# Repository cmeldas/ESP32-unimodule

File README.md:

# ESP32 universal PCB for home automation

# Using TTGO-T Display 
https://github.com/Xinyuan-LilyGO/TTGO-T-Display

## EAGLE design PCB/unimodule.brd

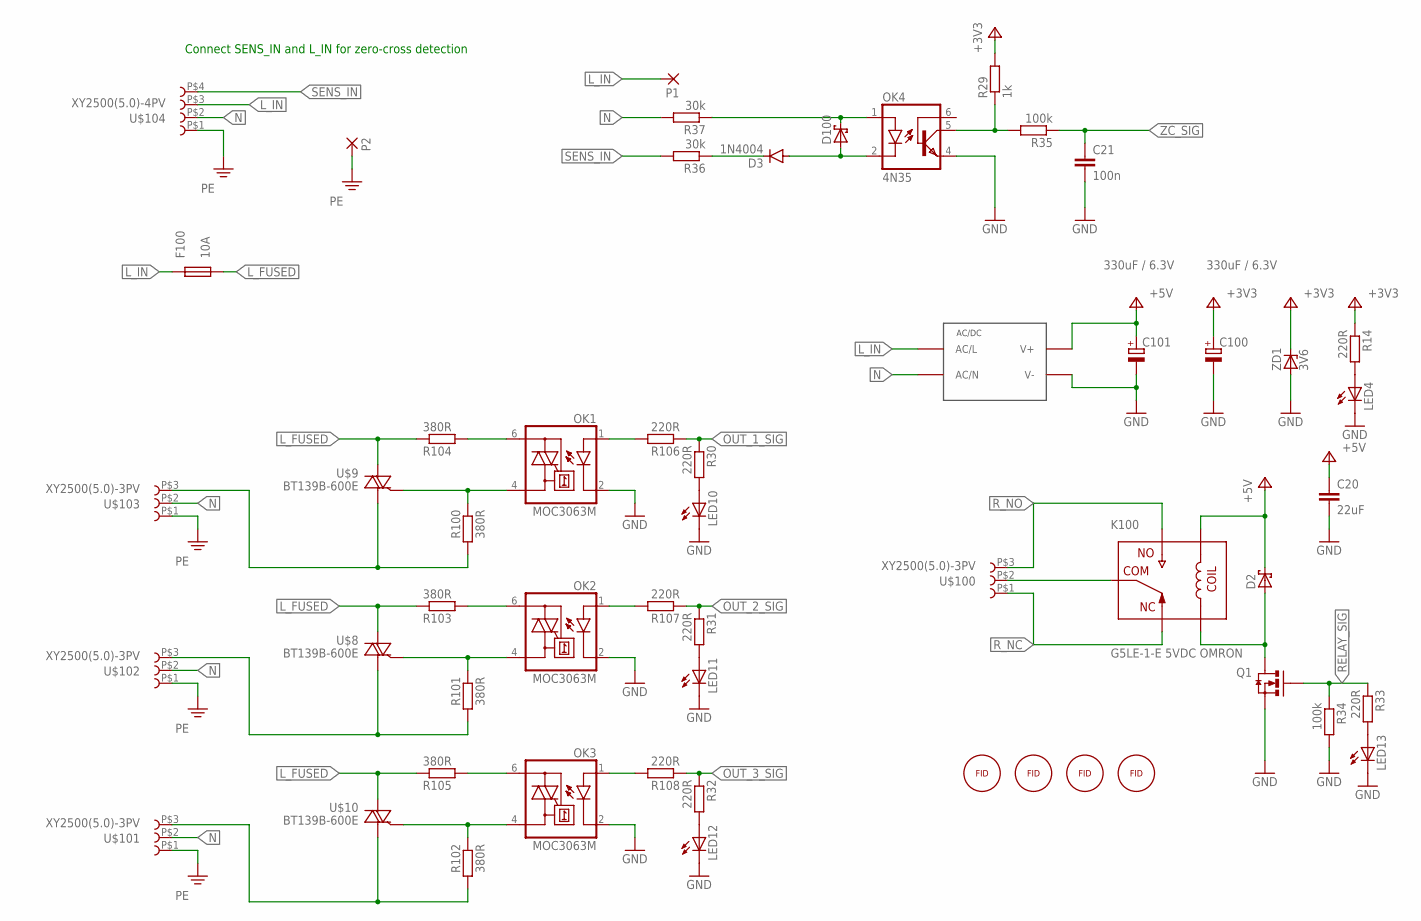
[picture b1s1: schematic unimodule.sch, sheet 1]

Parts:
C20: 22uF; C1206
C21: 100n; C0603
C100: 330uF / 6.3V; E2,5-7
C101: 330uF / 6.3V; E2,5-6
D2: PMEG4005EH; SOD123F
D3: 1N4004; DO41-10
D100: BAT46; SOD123F
F100: 10A; SCHURTER_0751.0056_5X20
FD1, FD2, FD100, FD101: FIDUCIAL-MARKER2MM; 1-2MM-FIDUCIAL
K100: G5LE-1-E 5VDC OMRON; JSM1-12V-5
LED4, LED10, LED11, LED12, LED13: LED0603; LED-0603
OK1, OK2, OK3: MOC3063M; DIL06
OK4: 4N35; DIL06
P1: WIRE-PAD1MM; THT-PAD_0.5MM
P2: WIRE-PAD3MM; 6MM2
Q1: 2N7002; PG-SOT23
R14, R30, R31, R32, R33, R106, R107, R108: 220R; R0603
R29: 1k; R0603
R34, R35: 100k; R0603
R36, R37: 30k; 0207/10
R100, R101, R102, R103, R104, R105: 380R; R1206
U$8, U$9, U$10: BT139B-600E; D2PACK
U$100, U$101, U$102, U$103: XY2500(5.0)-3PV; XY2500V-B_3P
U$104: XY2500(5.0)-4PV; XY2500V-B_4P
U$105: IRM-03-05; IRM-03
ZD1: 3V6; SOD323-W

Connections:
+3V3: C100.+, R14.1, R29.2, ZD1.C; also elsewhere on the board
+5V: C20.1, C101.+, D2.C, K100.2, U$105.V+; also elsewhere on the board
GND: C20.2, C21.2, C100.-, C101.-, LED4.C, LED10.C, LED11.C, LED12.C, LED13.C, OK1.2 (C), OK2.2 (C), OK3.2 (C), OK4.4 (EMI), Q1.2 (S), R34.2, U$105.V-, ZD1.A; also elsewhere on the board
L_FUSED: F100.I_1 (1), F100.I_2 (1), F100.I_3 (1), R103.1, R104.1, R105.1, U$8.2 (A2), U$9.2 (A2), U$10.2 (A2)
L_IN: F100.O_1 (2), F100.O_2 (2), F100.O_3 (2), P1.P$1, U$104.P$3 (3), U$105.AC/L
L_OUT_1: R100.2, U$9.1 (A1), U$103.P$3 (3)
L_OUT_2: R101.2, U$8.1 (A1), U$102.P$3 (3)
L_OUT_3: R102.2, U$10.1 (A1), U$101.P$3 (3)
N: R37.2, U$101.P$2 (2), U$102.P$2 (2), U$103.P$2 (2), U$104.P$2 (2), U$105.AC/N
unnamed: D3.A, D100.A, OK4.2 (C)
unnamed: D3.C, R36.1
unnamed: D100.C, OK4.1 (A), R37.1
unnamed: OK3.6 (A2), R105.2
unnamed: OK3.4 (A1), R102.1, U$10.3 (G)
unnamed: OK2.6 (A2), R103.2
unnamed: OK3.1 (A), R108.2
unnamed: OK2.4 (A1), R101.1, U$8.3 (G)
unnamed: OK2.1 (A), R107.2
unnamed: OK1.6 (A2), R104.2
unnamed: OK1.4 (A1), R100.1, U$9.3 (G)
unnamed: OK1.1 (A), R106.2
unnamed: LED10.A, R30.2
unnamed: LED11.A, R31.2
unnamed: LED12.A, R32.2
unnamed: D2.A, K100.5, Q1.3 (D)
unnamed: LED13.A, R33.2
unnamed: LED4.A, R14.2
OUT_1_SIG: R30.1, R106.1; also elsewhere on the board
OUT_2_SIG: R31.1, R107.1; also elsewhere on the board
OUT_3_SIG: R32.1, R108.1; also elsewhere on the board
PE: P2.P$1, P2.P$2, P2.P$5, P2.P$6, P2.P$7, P2.P$8, P2.P$9, P2.P$10, P2.P$11, U$101.P$1 (1), U$102.P$1 (1), U$103.P$1 (1), U$104.P$1 (1)
RELAY_SIG: Q1.1 (G), R33.1, R34.1; also elsewhere on the board
R_C: K100.1, U$100.P$2 (2)
R_NC: K100.4, U$100.P$1 (1)
R_NO: K100.3, U$100.P$3 (3)
SENS_IN: R36.2, U$104.P$4 (4)
ZC: OK4.5 (COL), R29.1, R35.2
ZC_SIG: C21.1, R35.1; also elsewhere on the board

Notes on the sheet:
Connect SENS_IN and L_IN for zero-cross detection

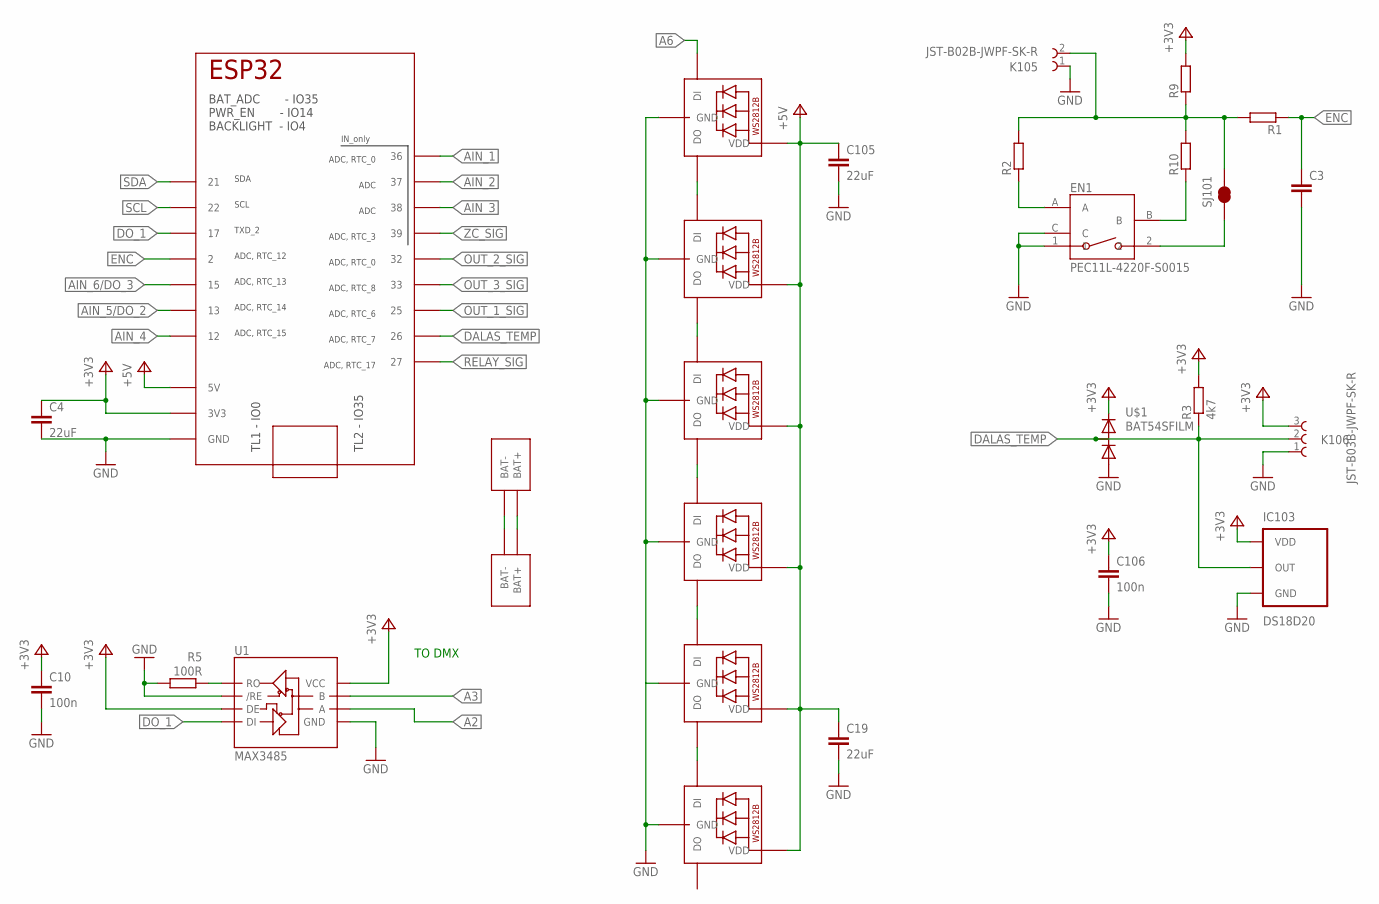
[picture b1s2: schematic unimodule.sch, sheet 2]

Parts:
C3: C-EUC0603; C0603
C4, C19, C105: 22uF; C1206
C10, C106: 100n; C0603
C11: DISP_BATSMD; BAT_SMD
C107: DISP_BAT2,54; BAT_THT_254
EN1: PEC11L-4220F-S0015
IC1: TTGO_DISP; TTGO_DISP_DEFAULT
IC103: DS18D20; TO92
K105: JST-B02B-JWPF-SK-R
K106: JST-B03B-JWPF-SK-R
LED1, LED2, LED3, LED5, LED6, LED14: WS2812B5050; WS2812B
R1, R2, R9, R10: R-EU_R0603; R0603
R3: 4k7; R0603
R5: 100R; R0603
SJ101: NET-TIE; SMD-JUMPER-TIE
U1: MAX3485; SO08
U$1: BAT54SFILM; PG-SOT23

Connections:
+3V3: C4.1, C10.1, C106.1, IC1.3V3_1 (3V3), IC1.3V3_2 (3V3), IC103.3 (VDD), K106.3, R3.2, R9.2, U1.3 (DE), U1.8 (VCC), U$1.2 (C); also elsewhere on the board
+5V: C19.1, C105.1, IC1.5V, LED1.1-VDD (VDD), LED2.1-VDD (VDD), LED3.1-VDD (VDD), LED5.1-VDD (VDD), LED6.1-VDD (VDD), LED14.1-VDD (VDD); also elsewhere on the board
A2: U1.6 (A); also elsewhere on the board
A3: U1.7 (B); also elsewhere on the board
A6: LED1.4-DIN (DI); also elsewhere on the board
AIN_1: IC1.36; also elsewhere on the board
AIN_2: IC1.37; also elsewhere on the board
AIN_3: IC1.38; also elsewhere on the board
AIN_4: IC1.12; also elsewhere on the board
AIN_5/DO_2: IC1.13; also elsewhere on the board
AIN_6/DO_3: IC1.15; also elsewhere on the board
BAT+: C11.BAT+, C107.BAT+
BAT-: C11.BAT-, C107.BAT-
DALAS_TEMP: IC1.26, IC103.2 (OUT), K106.2, R3.1, U$1.3 (COMMON)
DO_1: IC1.17, U1.4 (DI); also elsewhere on the board
ENC: C3.1, IC1.2, R1.1
ENC_2: K105.2, R1.2, R2.2, R9.1, R10.2, SJ101.2
GND: C3.2, C4.2, C10.2, C19.2, C105.2, C106.2, EN1.1, EN1.C, IC1.GND_1 (GND), IC1.GND_2 (GND), IC1.GND_3 (GND), IC1.GND_4 (GND), IC1.GND_5 (GND), IC103.1 (GND), K105.1, K106.1, LED1.3-GND (GND), LED2.3-GND (GND), LED3.3-GND (GND), LED5.3-GND (GND), LED6.3-GND (GND), LED14.3-GND (GND), R5.2, U1.2 (/RE), U1.5 (GND), U$1.1 (A); also elsewhere on the board
unnamed: EN1.A, R2.1
unnamed: EN1.B, R10.1
unnamed: EN1.2, SJ101.1
unnamed: LED1.2-DOUT (DO), LED2.4-DIN (DI)
unnamed: LED2.2-DOUT (DO), LED3.4-DIN (DI)
unnamed: LED3.2-DOUT (DO), LED5.4-DIN (DI)
unnamed: LED5.2-DOUT (DO), LED6.4-DIN (DI)
unnamed: LED6.2-DOUT (DO), LED14.4-DIN (DI)
unnamed: R5.1, U1.1 (RO)
OUT_1_SIG: IC1.25; also elsewhere on the board
OUT_2_SIG: IC1.32; also elsewhere on the board
OUT_3_SIG: IC1.33; also elsewhere on the board
RELAY_SIG: IC1.27; also elsewhere on the board
SCL: IC1.22; also elsewhere on the board
SDA: IC1.21; also elsewhere on the board
ZC_SIG: IC1.39; also elsewhere on the board

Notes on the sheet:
TO DMX

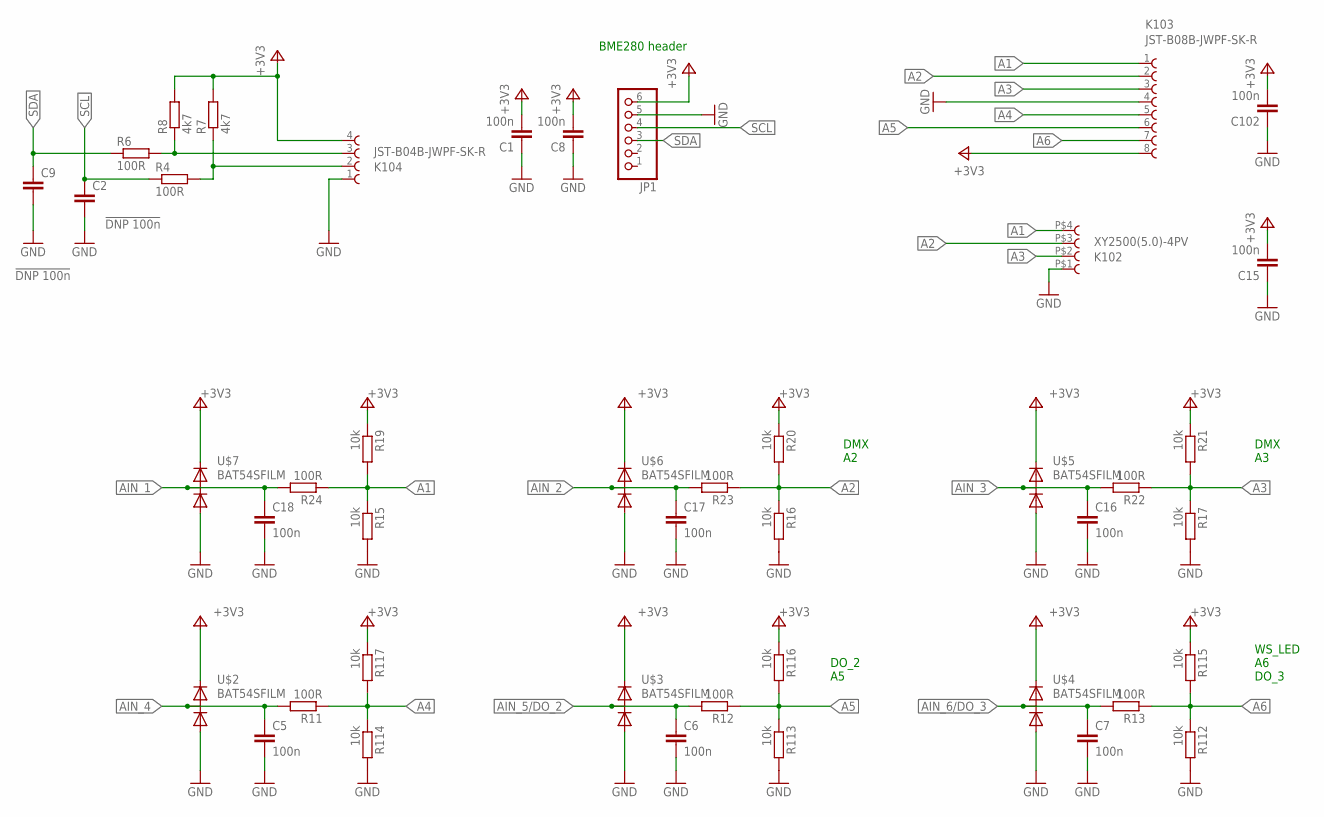
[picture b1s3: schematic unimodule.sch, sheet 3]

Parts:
C1, C5, C6, C7, C8, C15, C16, C17, C18, C102: 100n; C0603
C2, C9: !DNP 100n; C0603
JP1: PINHD-1X6; 1X06
K102: XY2500(5.0)-4PV; XY2500V-B_4P
K103: JST-B08B-JWPF-SK-R
K104: JST-B04B-JWPF-SK-R
R4, R6, R11, R12, R13, R22, R23, R24: 100R; R0603
R7, R8: 4k7; R0603
R15, R16, R17, R19, R20, R21, R112, R113, R114, R115, R116, R117: 10k; R0603
U$2, U$3, U$4, U$5, U$6, U$7: BAT54SFILM; PG-SOT23

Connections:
+3V3: C1.2, C8.2, C15.2, C102.2, JP1.6, K103.8, K104.4, R7.2, R8.2, R19.1, R20.1, R21.1, R115.1, R116.1, R117.1, U$2.2 (C), U$3.2 (C), U$4.2 (C), U$5.2 (C), U$6.2 (C), U$7.2 (C); also elsewhere on the board
A1: K102.P$4 (4), K103.1, R15.1, R19.2, R24.1
A2: K102.P$3 (3), K103.2, R16.1, R20.2, R23.1; also elsewhere on the board
A3: K102.P$2 (2), K103.3, R17.1, R21.2, R22.1; also elsewhere on the board
A4: K103.5, R11.1, R114.1, R117.2
A5: K103.6, R12.1, R113.1, R116.2
A6: K103.7, R13.1, R112.1, R115.2; also elsewhere on the board
AIN_1: C18.1, R24.2, U$7.3 (COMMON); also elsewhere on the board
AIN_2: C17.1, R23.2, U$6.3 (COMMON); also elsewhere on the board
AIN_3: C16.1, R22.2, U$5.3 (COMMON); also elsewhere on the board
AIN_4: C5.1, R11.2, U$2.3 (COMMON); also elsewhere on the board
AIN_5/DO_2: C6.1, R12.2, U$3.3 (COMMON); also elsewhere on the board
AIN_6/DO_3: C7.1, R13.2, U$4.3 (COMMON); also elsewhere on the board
GND: C1.1, C2.2, C5.2, C6.2, C7.2, C8.1, C9.2, C15.1, C16.2, C17.2, C18.2, C102.1, JP1.5, K102.P$1 (1), K103.4, K104.1, R15.2, R16.2, R17.2, R112.2, R113.2, R114.2, U$2.1 (A), U$3.1 (A), U$4.1 (A), U$5.1 (A), U$6.1 (A), U$7.1 (A); also elsewhere on the board
SCL: C2.1, JP1.4, R4.1; also elsewhere on the board
SCL_P: K104.2, R4.2, R7.1
SDA: C9.1, JP1.3, R6.1; also elsewhere on the board
SDA_P: K104.3, R6.2, R8.1

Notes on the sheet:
BME280 header
WS_LED A6 DO_3
DMX A3
DMX A2
DO_2 A5

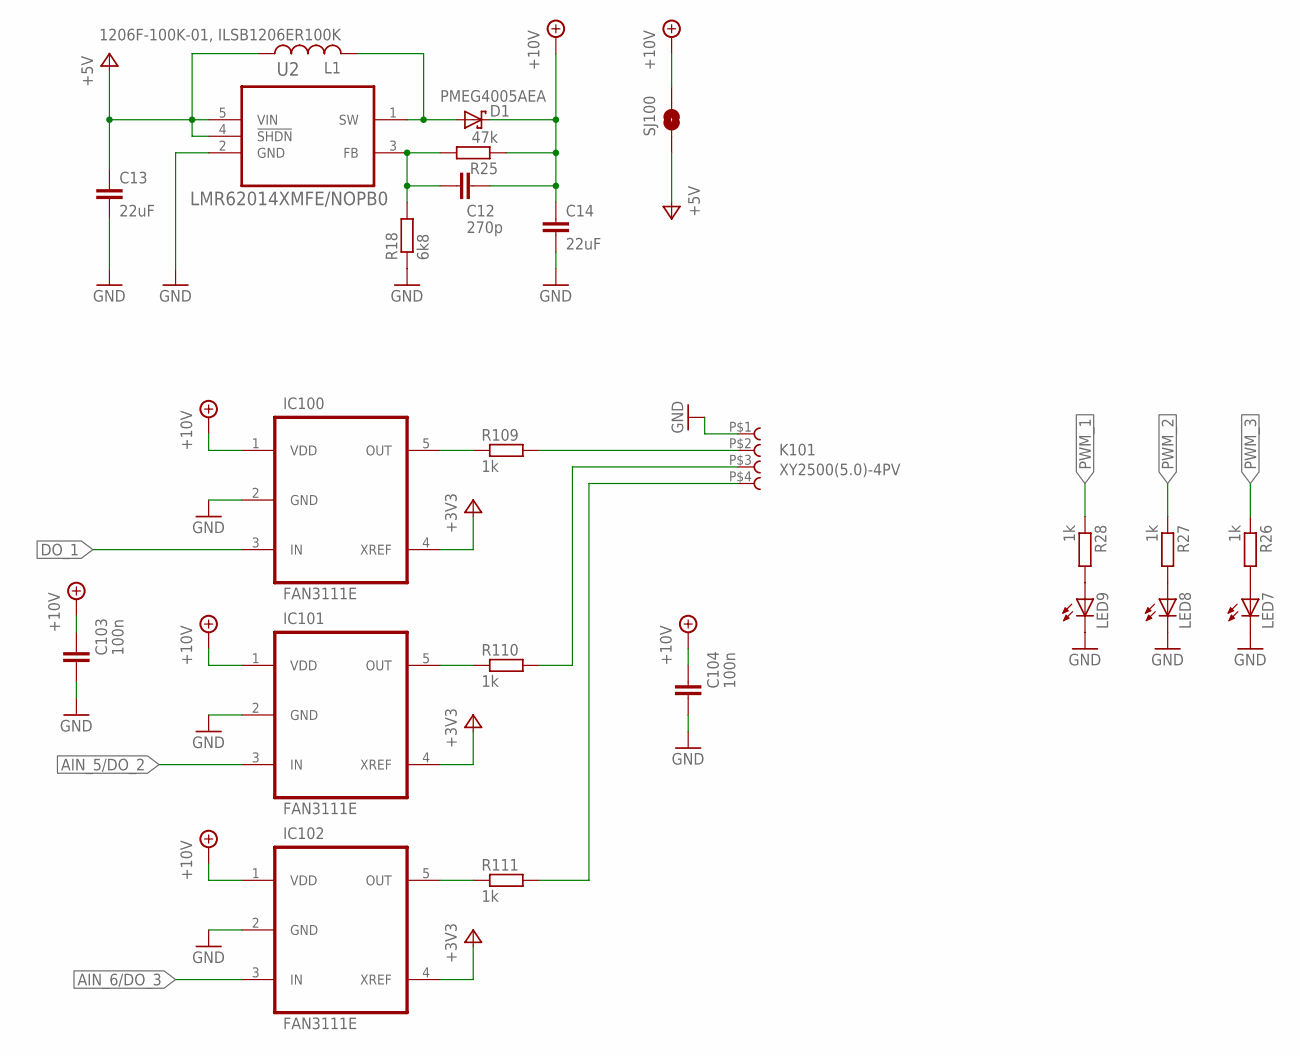
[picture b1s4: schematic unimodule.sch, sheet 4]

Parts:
C12: 270p; C0603
C13, C14: 22uF; C1206
C103, C104: 100n; C0603
D1: PMEG4005AEA; SOD123F
IC100, IC101, IC102: FAN3111E; SOT23-5
K101: XY2500(5.0)-4PV; XY2500V-B_4P
L1: 1206F-100K-01, ILSB1206ER100K; C3216
LED7, LED8, LED9: LED0603; LED-0603
R18: 6k8; R0603
R25: 47k; R0603
R26, R27, R28: 1k; R0603
R109, R110, R111: 1k; R1206
SJ100: SMD-JUMPER
U2: LMR62014XMFE/NOPB0; SOT23-5

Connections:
+3V3: IC100.4 (XREF), IC101.4 (XREF), IC102.4 (XREF); also elsewhere on the board
+5V: C13.1, L1.1, SJ100.1, U2.4 (!SHDN), U2.5 (VIN); also elsewhere on the board
+10V: C12.2, C14.1, C103.2, C104.2, D1.C, IC100.1 (VDD), IC101.1 (VDD), IC102.1 (VDD), R25.1, SJ100.2
AIN_5/DO_2: IC101.3 (IN); also elsewhere on the board
AIN_6/DO_3: IC102.3 (IN); also elsewhere on the board
DO_1: IC100.3 (IN); also elsewhere on the board
GND: C13.2, C14.2, C103.1, C104.1, IC100.2 (GND), IC101.2 (GND), IC102.2 (GND), K101.P$1 (1), LED7.C, LED8.C, LED9.C, R18.1, U2.2 (GND); also elsewhere on the board
unnamed: IC101.5 (OUT), R110.1
unnamed: D1.A, L1.2, U2.1 (SW)
unnamed: LED9.A, R28.2
unnamed: LED8.A, R27.2
unnamed: IC100.5 (OUT), R109.1
unnamed: LED7.A, R26.2
unnamed: IC102.5 (OUT), R111.1
unnamed: C12.1, R18.2, R25.2, U2.3 (FB)
PWM_1: K101.P$2 (2), R28.1, R109.2
PWM_2: K101.P$3 (3), R27.1, R110.2
PWM_3: K101.P$4 (4), R26.1, R111.2

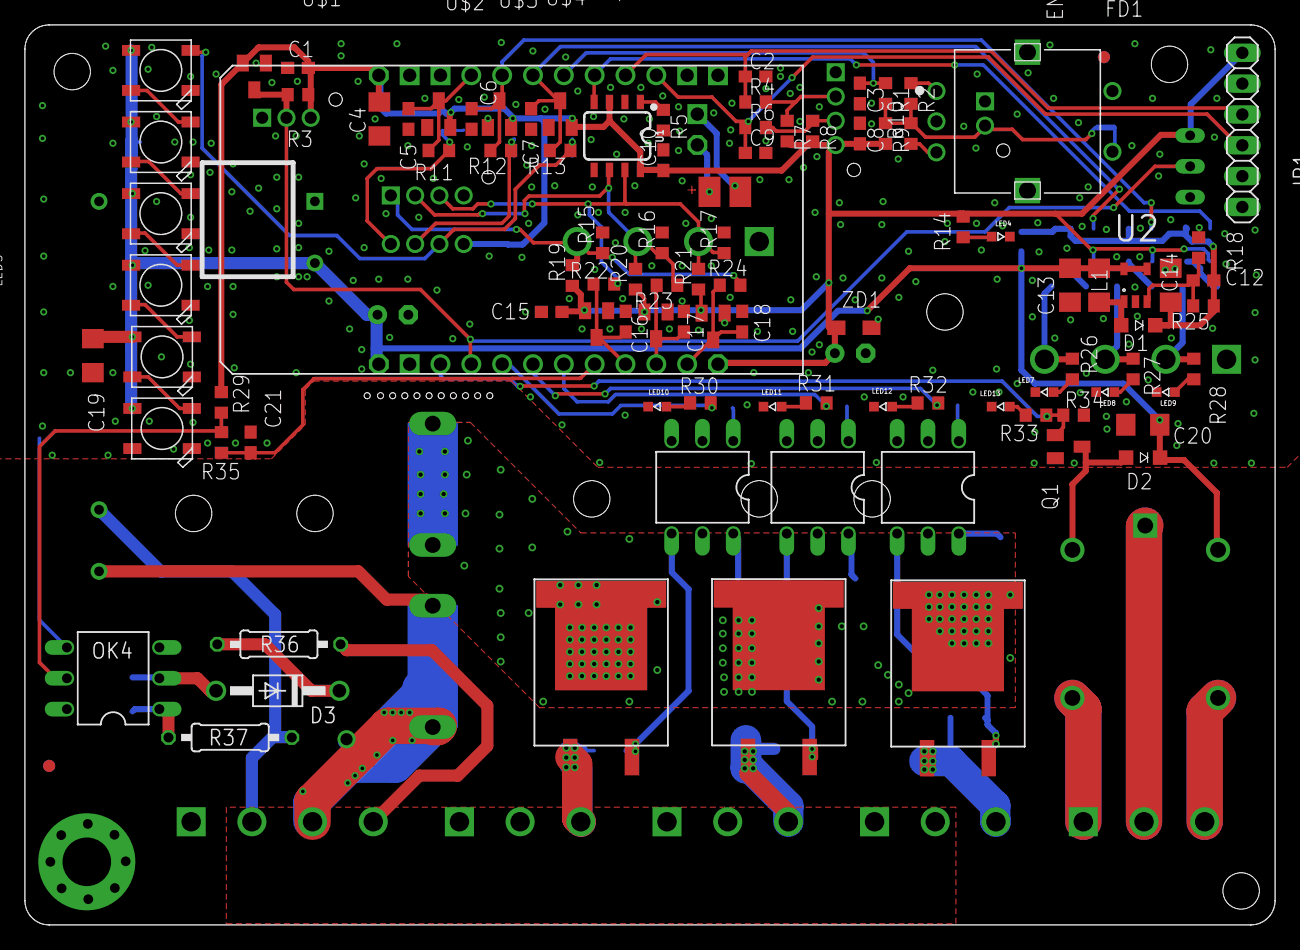
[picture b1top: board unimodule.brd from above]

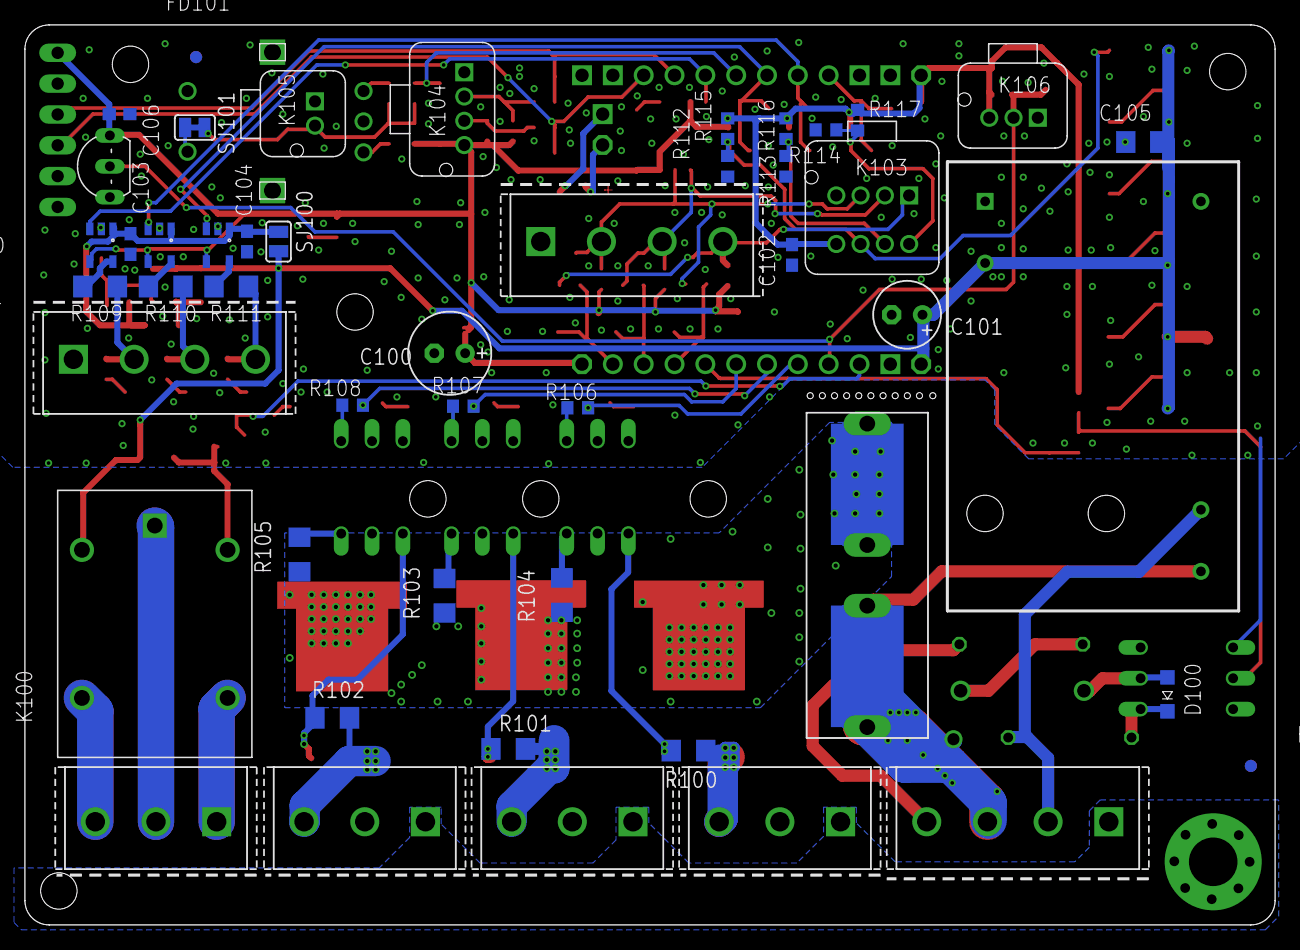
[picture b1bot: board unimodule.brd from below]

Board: 2 copper layers, 103.0 x 74.2 mm, 150 parts (49 on the bottom side), 81 nets.

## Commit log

2020-03-21 WIP, schematic almost done
2020-03-21 almost ready
2020-03-22 Fix components height
2020-03-22 add connector description
2020-03-26 add status LEDs
2020-03-29 some minor changes, tweaks
2020-03-30 silk screen organize

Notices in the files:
parts and their libraries:
SparkFun-IC-Comms: Licensing: Creative Commons ShareAlike 4.0 International - https://creativecommons.org/licenses/by-sa/4.0
